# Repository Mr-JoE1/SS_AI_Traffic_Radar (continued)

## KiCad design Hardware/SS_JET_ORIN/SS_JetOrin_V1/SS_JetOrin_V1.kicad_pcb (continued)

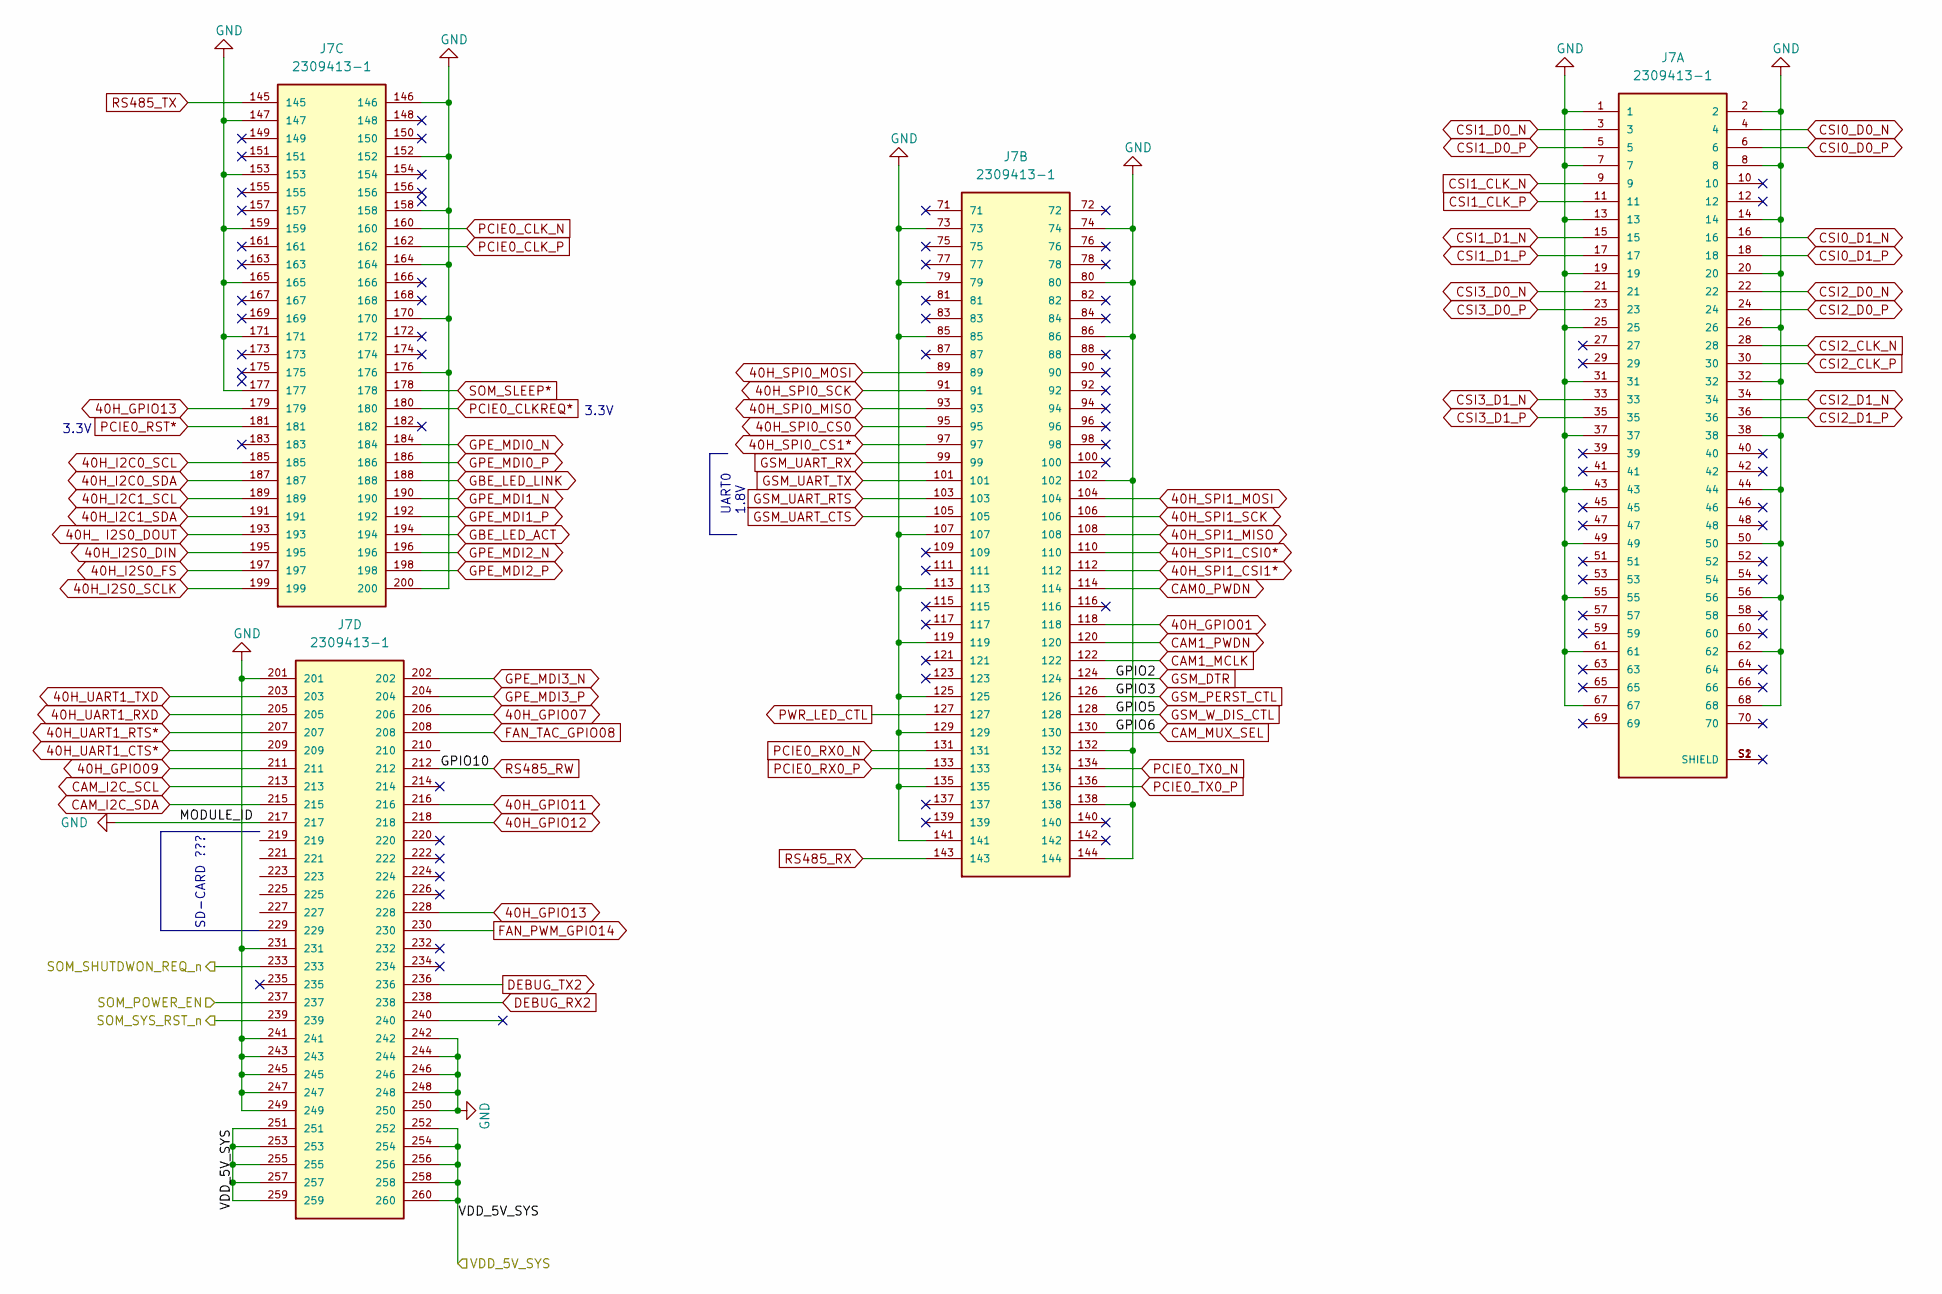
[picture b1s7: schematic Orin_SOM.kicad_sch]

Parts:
J7: 2309413-1; TE_2309413-1

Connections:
40H_ I2S0_DOUT: J7.193; also elsewhere on the board
40H_GPIO01: J7.118; also elsewhere on the board
40H_GPIO07: J7.206; also elsewhere on the board
40H_GPIO09: J7.211; also elsewhere on the board
40H_GPIO11: J7.216; also elsewhere on the board
40H_GPIO12: J7.218; also elsewhere on the board
40H_GPIO13: J7.179, J7.228; also elsewhere on the board
40H_I2C0_SCL: J7.185
40H_I2C0_SDA: J7.187
40H_I2C1_SCL: J7.189
40H_I2C1_SDA: J7.191
40H_I2S0_DIN: J7.195; also elsewhere on the board
40H_I2S0_FS: J7.197; also elsewhere on the board
40H_I2S0_SCLK: J7.199; also elsewhere on the board
40H_SPI0_CS0: J7.95; also elsewhere on the board
40H_SPI0_CS1*: J7.97; also elsewhere on the board
40H_SPI0_MISO: J7.93; also elsewhere on the board
40H_SPI0_MOSI: J7.89; also elsewhere on the board
40H_SPI0_SCK: J7.91; also elsewhere on the board
40H_SPI1_CSI0*: J7.110; also elsewhere on the board
40H_SPI1_CSI1*: J7.112; also elsewhere on the board
40H_SPI1_MISO: J7.108; also elsewhere on the board
40H_SPI1_MOSI: J7.104; also elsewhere on the board
40H_SPI1_SCK: J7.106; also elsewhere on the board
40H_UART1_CTS*: J7.209; also elsewhere on the board
40H_UART1_RTS*: J7.207; also elsewhere on the board
40H_UART1_RXD: J7.205; also elsewhere on the board
40H_UART1_TXD: J7.203; also elsewhere on the board
/Orin_SOM/SOM_POWER_EN: J7.237; also elsewhere on the board
/PSUs/P_Seq_M/SHUT_REQ: J7.233; also elsewhere on the board
/PSUs/P_Seq_M/SYS_RST: J7.239; also elsewhere on the board
/VDD_5V_SYS: J7.251, J7.252, J7.253, J7.254, J7.255, J7.256, J7.257, J7.258, J7.259, J7.260; also elsewhere on the board
CAM0_PWDN: J7.114; also elsewhere on the board
CAM1_MCLK: J7.122; also elsewhere on the board
CAM1_PWDN: J7.120; also elsewhere on the board
CAM_I2C_SCL: J7.213; also elsewhere on the board
CAM_I2C_SDA: J7.215; also elsewhere on the board
CAM_MUX_SEL: J7.130; also elsewhere on the board
CSI0_D0_N: J7.4; also elsewhere on the board
CSI0_D0_P: J7.6; also elsewhere on the board
CSI0_D1_N: J7.16; also elsewhere on the board
CSI0_D1_P: J7.18; also elsewhere on the board
CSI1_CLK_N: J7.9; also elsewhere on the board
CSI1_CLK_P: J7.11; also elsewhere on the board
CSI1_D0_N: J7.3; also elsewhere on the board
CSI1_D0_P: J7.5; also elsewhere on the board
CSI1_D1_N: J7.15; also elsewhere on the board
CSI1_D1_P: J7.17; also elsewhere on the board
CSI2_CLK_N: J7.28; also elsewhere on the board
CSI2_CLK_P: J7.30; also elsewhere on the board
CSI2_D0_N: J7.22; also elsewhere on the board
CSI2_D0_P: J7.24; also elsewhere on the board
CSI2_D1_N: J7.34; also elsewhere on the board
CSI2_D1_P: J7.36; also elsewhere on the board
CSI3_D0_N: J7.21; also elsewhere on the board
CSI3_D0_P: J7.23; also elsewhere on the board
CSI3_D1_N: J7.33; also elsewhere on the board
CSI3_D1_P: J7.35; also elsewhere on the board
DEBUG_RX2: J7.238; also elsewhere on the board
DEBUG_TX2: J7.236; also elsewhere on the board
FAN_PWM_GPIO14: J7.230; also elsewhere on the board
FAN_TAC_GPIO08: J7.208; also elsewhere on the board
GBE_LED_ACT: J7.194; also elsewhere on the board
GBE_LED_LINK: J7.188; also elsewhere on the board
GND: J7.1, J7.2, J7.7, J7.8, J7.13, J7.14, J7.19, J7.20, J7.25, J7.26, J7.31, J7.32, J7.37, J7.38, J7.43, J7.44, J7.49, J7.50, J7.55, J7.56, J7.61, J7.62, J7.67, J7.68, J7.73, J7.74, J7.79, J7.80, J7.85, J7.86, J7.102, J7.107, J7.113, J7.119, J7.125, J7.129, J7.132, J7.135, J7.138, J7.141, J7.144, J7.146, J7.147, J7.152, J7.153, J7.158, J7.159, J7.164, J7.165, J7.170, J7.171, J7.176, J7.177, J7.200, J7.201, J7.217, J7.231, J7.241, J7.242, J7.243, J7.244, J7.245, J7.246, J7.247, J7.248, J7.249, J7.250; also elsewhere on the board
GPE_MDI0_N: J7.184; also elsewhere on the board
GPE_MDI0_P: J7.186; also elsewhere on the board
GPE_MDI1_N: J7.190; also elsewhere on the board
GPE_MDI1_P: J7.192; also elsewhere on the board
GPE_MDI2_N: J7.196; also elsewhere on the board
GPE_MDI2_P: J7.198; also elsewhere on the board
GPE_MDI3_N: J7.202; also elsewhere on the board
GPE_MDI3_P: J7.204; also elsewhere on the board
GSM_DTR: J7.124; also elsewhere on the board
GSM_PERST_CTL: J7.126; also elsewhere on the board
GSM_UART_CTS: J7.105; also elsewhere on the board
GSM_UART_RTS: J7.103; also elsewhere on the board
GSM_UART_RX: J7.99; also elsewhere on the board
GSM_UART_TX: J7.101; also elsewhere on the board
GSM_W_DIS_CTL: J7.128; also elsewhere on the board
PCIE0_CLKREQ*: J7.180; also elsewhere on the board
PCIE0_CLK_N: J7.160; also elsewhere on the board
PCIE0_CLK_P: J7.162; also elsewhere on the board
PCIE0_RST*: J7.181; also elsewhere on the board
PCIE0_RX0_N: J7.131; also elsewhere on the board
PCIE0_RX0_P: J7.133; also elsewhere on the board
PCIE0_TX0_N: J7.134; also elsewhere on the board
PCIE0_TX0_P: J7.136; also elsewhere on the board
PWR_LED_CTL: J7.127; also elsewhere on the board
RS485_RW: J7.212; also elsewhere on the board
RS485_RX: J7.143; also elsewhere on the board
RS485_TX: J7.145; also elsewhere on the board
SOM_SLEEP*: J7.178; also elsewhere on the board

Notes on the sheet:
3.3V
SD-CARD ???
UART0 1.8V

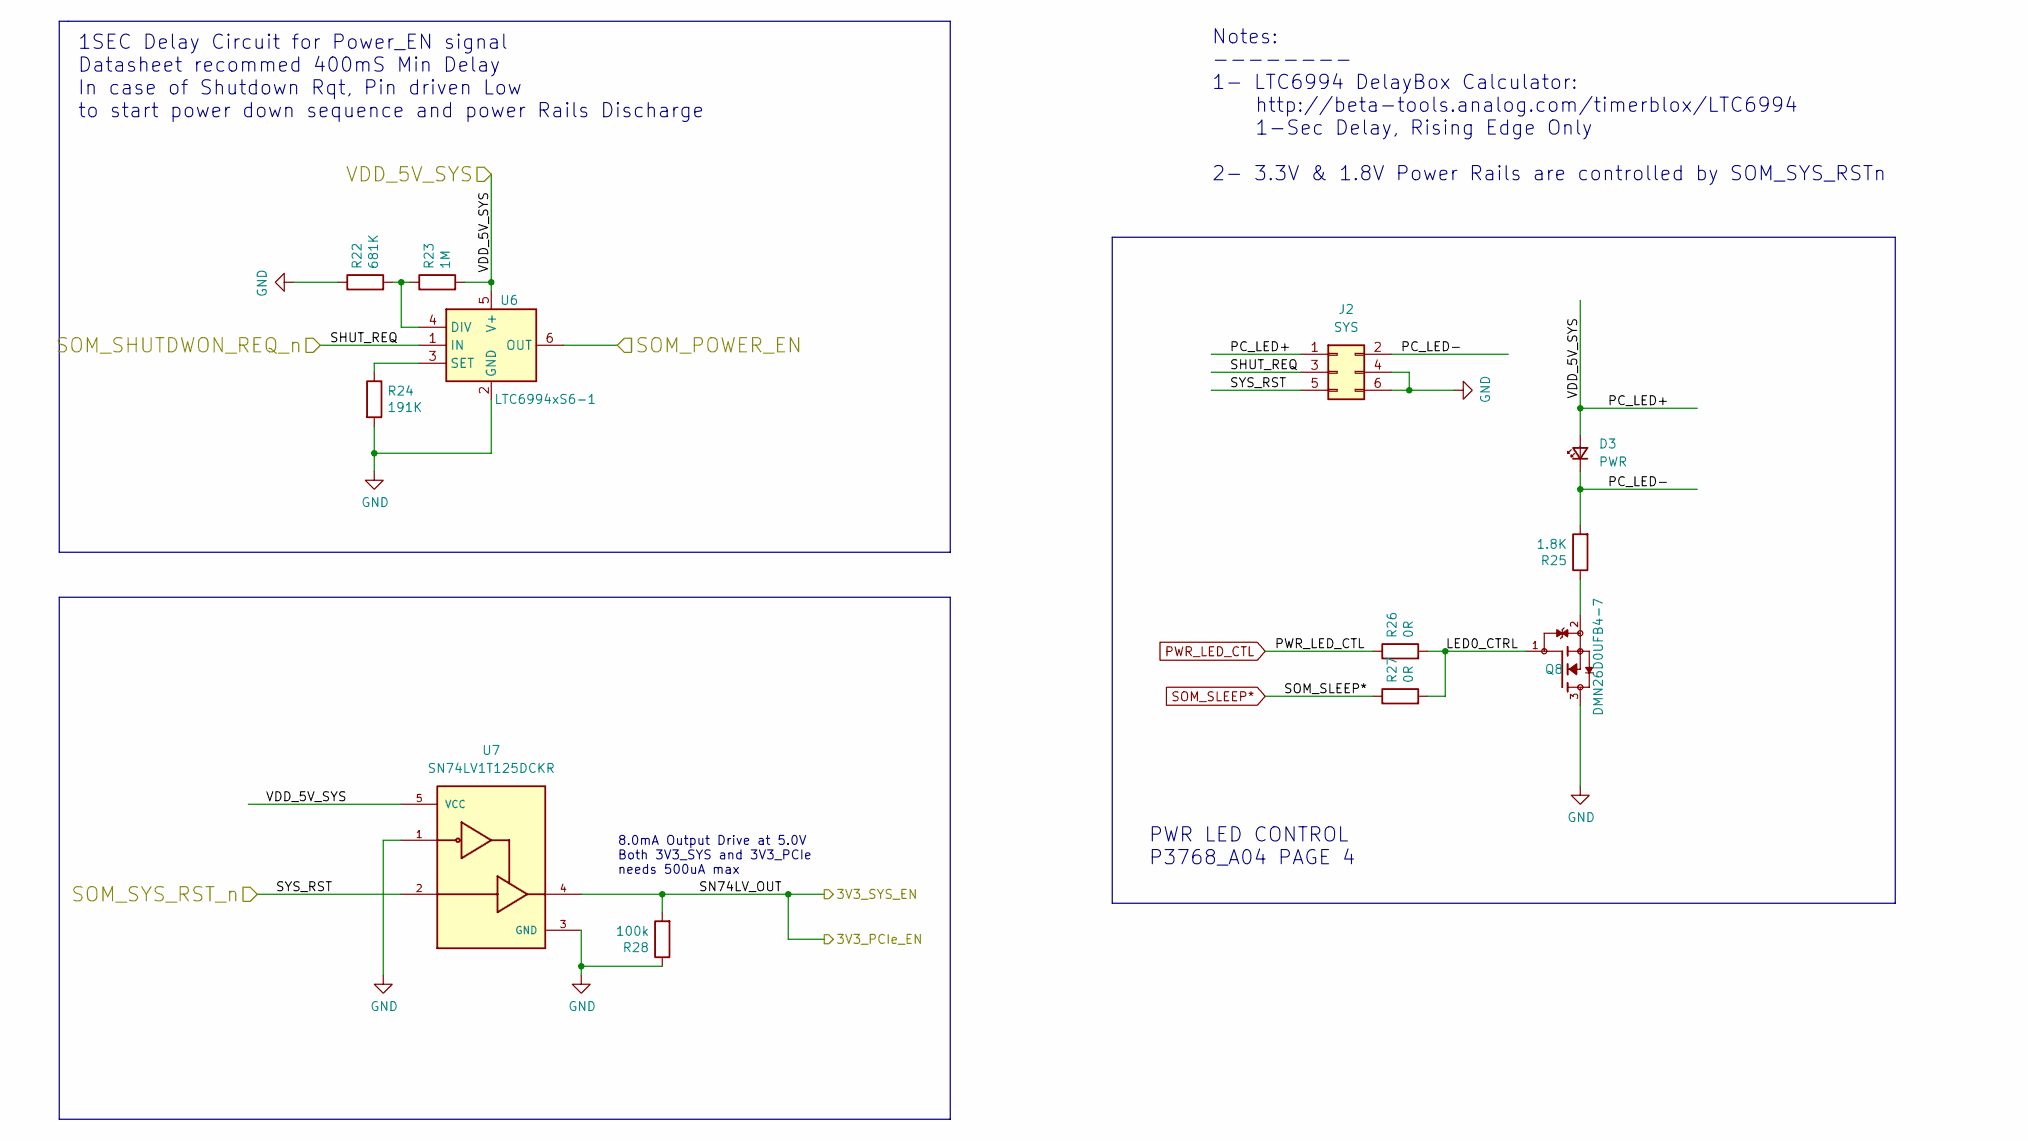
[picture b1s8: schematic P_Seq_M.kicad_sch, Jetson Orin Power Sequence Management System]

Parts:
D3: PWR; LED_0402_1005Metric; LCSC C130719
J2: SYS; PinHeader_2x03_P2.54mm_Vertical
Q8: DMN26D0UFB4-7; TRXDFN100X60X40-3N; PARTREV 12-2; LCSC C260867
R22: 681K; R_0201_0603Metric; Part Description Resistor 12K M1005 1% 63mW; LCSC C423447
R23: 1M; R_0201_0603Metric; Part Description Resistor 12K M1005 1% 63mW; LCSC C2105628
R24: 191K; R_0201_0603Metric; Part Description Resistor 12K M1005 1% 63mW; LCSC C778415
R25: 1.8K; R_0201_0603Metric; Part Description Resistor 12K M1005 1% 63mW; LCSC C171943
R26, R27: 0R; R_0201_0603Metric; Part Description Resistor 12K M1005 1% 63mW; LCSC C106228
R28: 100k; R_0201_0603Metric; Part Description Resistor 12K M1005 1% 63mW; LCSC C106224
U6: LTC6994xS6-1; TSOT-23-6; LCSC OUT_OS
U7: SN74LV1T125DCKR; SOT65P210X110-5N; PARTREV A; LCSC C75925

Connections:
/Orin_SOM/SOM_POWER_EN: U6.6 (OUT); also elsewhere on the board
/PSUs/3V3_PCIe_EN: R28.2, U7.4; also elsewhere on the board
/PSUs/P_Seq_M/LED0_CTRL: Q8.1, R26.2, R27.2
/PSUs/P_Seq_M/PC_LED-: D3.1 (K), J2.2, R25.2
/PSUs/P_Seq_M/SHUT_REQ: J2.3, U6.1 (IN); also elsewhere on the board
/PSUs/P_Seq_M/SYS_RST: J2.5, U7.2; also elsewhere on the board
/VDD_5V_SYS: D3.2 (A), J2.1, R23.2, U6.5 (V+), U7.5 (VCC); also elsewhere on the board
GND: J2.4, J2.6, Q8.3, R22.1, R24.2, R28.1, U6.2 (GND), U7.1, U7.3 (GND); also elsewhere on the board
unnamed: Q8.2, R25.1
unnamed: R22.2, R23.1, U6.4 (DIV)
unnamed: R24.1, U6.3 (SET)
PWR_LED_CTL: R26.1; also elsewhere on the board
SOM_SLEEP*: R27.1; also elsewhere on the board

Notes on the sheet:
1SEC Delay Circuit for Power_EN signal Datasheet recommed 400mS Min Delay In case of Shutdown Rqt, Pin driven Low to start power down sequence and power Rails Discharge
PWR LED CONTROL P3768_A04 PAGE 4
8.0mA Output Drive at 5.0V Both 3V3_SYS and 3V3_PCIe needs 500uA max
Notes: -------- 1- LTC6994 DelayBox Calculator: http://beta-tools.analog.com/timerblox/LTC6994 1-Sec Delay, Rising Edge Only 2- 3.3V & 1.8V Power Rails are controlled by SOM_SYS_RSTn

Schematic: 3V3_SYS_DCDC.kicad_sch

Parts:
C15: 470uF; Kemet _3760_H; LCSC C600599
C16: 100n; C_0201_0603Metric; LCSC C307380
C17: 470uF; CP_EIA-7343-31_Kemet-D; LCSC C116576
C18: 100n; C_0201_0603Metric; Part Description 0.1uF 10% 100V Ceramic Capacitor X5R 04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; LCSC C307380
C19: 33p; C_0201_0603Metric; LCSC C277477
C20: 10p; C_0201_0603Metric; LCSC C272871
Q4: DMN26D0UFB4-7; TRXDFN100X60X40-3N; PARTREV 12-2; LCSC C260867
Q5: DMN61D9UW; SOT65P210X110-3N; LCSC C151592
R6: 82K 1%; R_0201_0603Metric; LCSC C384402
R7: 51K; R_0201_0603Metric; LCSC C171974
R8: 470R; R_0201_0603Metric; LCSC C304545
R9: 47K 1%; R_0201_0603Metric; LCSC C138139
R10: 100K; R_0201_0603Metric; Part Description Resistor 12K M1005 1% 63mW; LCSC C106224
R11: 1.27; R_0201_0603Metric; Part Description Resistor 12K M1005 1% 63mW; LCSC C158692
TP3: TestPoint; TestPoint_Pad_D1.0mm
U3: MIC29302WU; TO-263-5_TabPin3; LCSC C11149

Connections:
/3v3_SYS: C17.1, C18.1, C19.1, C20.1, R6.1, R8.1, R11.1, TP3.1, U3.4 (VOUT); also elsewhere on the board
/PSUs/3V3_PCIe_EN: Q4.1, R7.1; also elsewhere on the board
/PSUs/+12v: C15.1, C16.1, U3.2 (VIN); also elsewhere on the board
/VDD_5V_SYS: R10.1; also elsewhere on the board
GND: C15.2, C16.2, C17.2, C18.2, C19.2, C20.2, Q4.2, Q5.2 (S), R8.2, R9.2, U3.3 (GND); also elsewhere on the board
unnamed: Q4.3, Q5.1 (G), R10.2
unnamed: Q5.3 (D), R11.2
unnamed: R6.2, R9.1, U3.5 (ADJ)
unnamed: R7.2, U3.1 (EN)

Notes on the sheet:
3A/3.3V PSU for PCIe Module NB: PCIe x1 takes a maximum of +12v @0.6A or +3.3v@3A , 10Watts combined
3V3_SYS Discharge Circuit - P3768 PAGE 10
LOW ESR

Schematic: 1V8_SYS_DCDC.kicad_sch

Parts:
C1: 4.7u; C_0201_0603Metric; LCSC C335103
C2: nf; C_0201_0603Metric
C3, C4, C5: 1u; C_0201_0603Metric; LCSC C87143
Q1: DMN26D0UFB4-7; TRXDFN100X60X40-3N; PARTREV 12-2; LCSC C260867
Q2: DMN61D9UW; SOT65P210X110-3N; LCSC C151592
R1: 100K; R_0201_0603Metric; Part Description Resistor 12K M1005 1% 63mW; LCSC C106224
R2: 5.6R; R_0201_0603Metric; Part Description Resistor 12K M1005 1% 63mW; LCSC C367405
TP6: TestPoint; TestPoint_Pad_D1.0mm
U1: AP2127K-1.8; SOT-23-5; LCSC C151375

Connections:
/1V8_SYS: C1.1, C2.1, R2.1, TP6.1, U1.5 (VOUT); also elsewhere on the board
/3v3_SYS: C3.1, C4.1, C5.1, U1.1 (VIN); also elsewhere on the board
/PSUs/3V3_PCIe_EN: Q1.1, U1.3 (EN); also elsewhere on the board
/VDD_5V_SYS: R1.1; also elsewhere on the board
GND: C1.2, C2.2, C3.2, C4.2, C5.2, Q1.2, Q2.2 (S), U1.2 (GND); also elsewhere on the board
unnamed: Q1.3, Q2.1 (G), R1.2
unnamed: Q2.3 (D), R2.2

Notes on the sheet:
1V8 Discharge Circuit - P3768 PAGE 11

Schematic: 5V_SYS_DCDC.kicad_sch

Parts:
C9, C10: 4.7uF; C_0402_1005Metric; Part Description 10uF 10% or 20% 35V Ceramic Capacitor X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; LCSC C2858031
C11, C14: 0.01uF; C_0201_0603Metric; LCSC C285010
C12: 330uF; CP_EIA-7343-31_Kemet-D; LCSC C105408
C13: 0.01uF; C_0201_0603Metric; Part Description 10uF 10% or 20% 35V Ceramic Capacitor X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; LCSC C285010
D2: SS54; D_SMA; LCSC C908681
L1: CDRH127/LDNP-150MC; L_12x12mm_H8mm; LCSC C879410
R4: 10K; R_0201_0603Metric; LCSC C106225
R5: 3.16K; R_0201_0603Metric; LCSC C367583
TP2: TestPoint; TestPoint_Pad_D1.0mm
U2: TPS5450DDAR; CONV_TPS5450DDAR; PARTREV D; LCSC C114425

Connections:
/PSUs/5V_SYS_DCDC/VSNS1: R4.2, R5.1, U2.4 (VSENSE)
/PSUs/+12v: C9.1, C10.1, C11.1, U2.7 (VIN); also elsewhere on the board
/VDD_5V_SYS: C12.1, C13.1, L1.2, R4.1, TP2.1; also elsewhere on the board
GND: C9.2, C10.2, C11.2, C12.2, C13.2, D2.1 (A), R5.2, U2.6 (GND), U2.9 (POWERPAD); also elsewhere on the board
unnamed: C14.1, U2.1 (BOOT)
unnamed: C14.2, D2.2 (K), L1.1, U2.8 (PH)

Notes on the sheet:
12V to 5V step down CONV 3A Normal Load 5A@MAX
-(P3768_PAGE 9) *They use 10A chip ! due to data sheet Orin SOM LOAD 5A MAX

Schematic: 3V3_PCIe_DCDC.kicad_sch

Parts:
C21, C27: 470uF; Kemet _3760_H; LCSC C600599
C22, C28: 100n; C_0201_0603Metric; LCSC C307380
C23, C29: 470uF; CP_EIA-7343-31_Kemet-D; LCSC C116576
C24, C30: 100n; C_0201_0603Metric; Part Description 0.1uF 10% 100V Ceramic Capacitor X5R 04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; LCSC C307380
C25, C31: 33p; C_0201_0603Metric; LCSC C277477
C26, C32: 10p; C_0201_0603Metric; LCSC C272871
Q6: DMN26D0UFB4-7; TRXDFN100X60X40-3N; PARTREV 12-2; LCSC C260867
Q7: DMN61D9UW; SOT65P210X110-3N; LCSC C151592
R12, R18: 82K 1%; R_0201_0603Metric; LCSC C384402
R13: 100K; R_0201_0603Metric; Part Description Resistor 12K M1005 1% 63mW; LCSC C106224
R14: 1.27; R_0201_0603Metric; Part Description Resistor 12K M1005 1% 63mW; LCSC C2691510
R15, R19: 51K; R_0201_0603Metric; LCSC C171974
R16, R20: 470R; R_0201_0603Metric; LCSC C304545
R17, R21: 47K 1%; R_0201_0603Metric; LCSC C138139
TP4, TP5: TestPoint; TestPoint_Pad_D1.0mm
U4, U5: MIC29302WU; TO-263-5_TabPin3; LCSC C11149

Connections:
/3v3_PCIe: C23.1, C24.1, C25.1, C26.1, C29.1, C30.1, C31.1, C32.1, R12.1, R14.1, R16.1, R18.1, R20.1, TP4.1, TP5.1, U4.4 (VOUT), U5.4 (VOUT); also elsewhere on the board
/PSUs/3V3_PCIe_DCDC/3V3_SYS_EN: Q6.1, R15.1, R19.1
/PSUs/+12v: C21.1, C22.1, C27.1, C28.1, U4.2 (VIN), U5.2 (VIN); also elsewhere on the board
/VDD_5V_SYS: R13.1; also elsewhere on the board
GND: C21.2, C22.2, C23.2, C24.2, C25.2, C26.2, C27.2, C28.2, C29.2, C30.2, C31.2, C32.2, Q6.2, Q7.2 (S), R16.2, R17.2, R20.2, R21.2, U4.3 (GND), U5.3 (GND); also elsewhere on the board
unnamed: Q6.3, Q7.1 (G), R13.2
unnamed: Q7.3 (D), R14.2
unnamed: R12.2, R17.1, U4.5 (ADJ)
unnamed: R15.2, U4.1 (EN)
unnamed: R18.2, R21.1, U5.5 (ADJ)
unnamed: R19.2, U5.1 (EN)

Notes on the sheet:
3V3_SYS Discharge Circuit - P3768 PAGE 10
3A/3.3V PSU for PCIe Module NB: PCIe x1 takes a maximum of +12v @0.6A or +3.3v@3A , 10Watts combined
LOW ESR

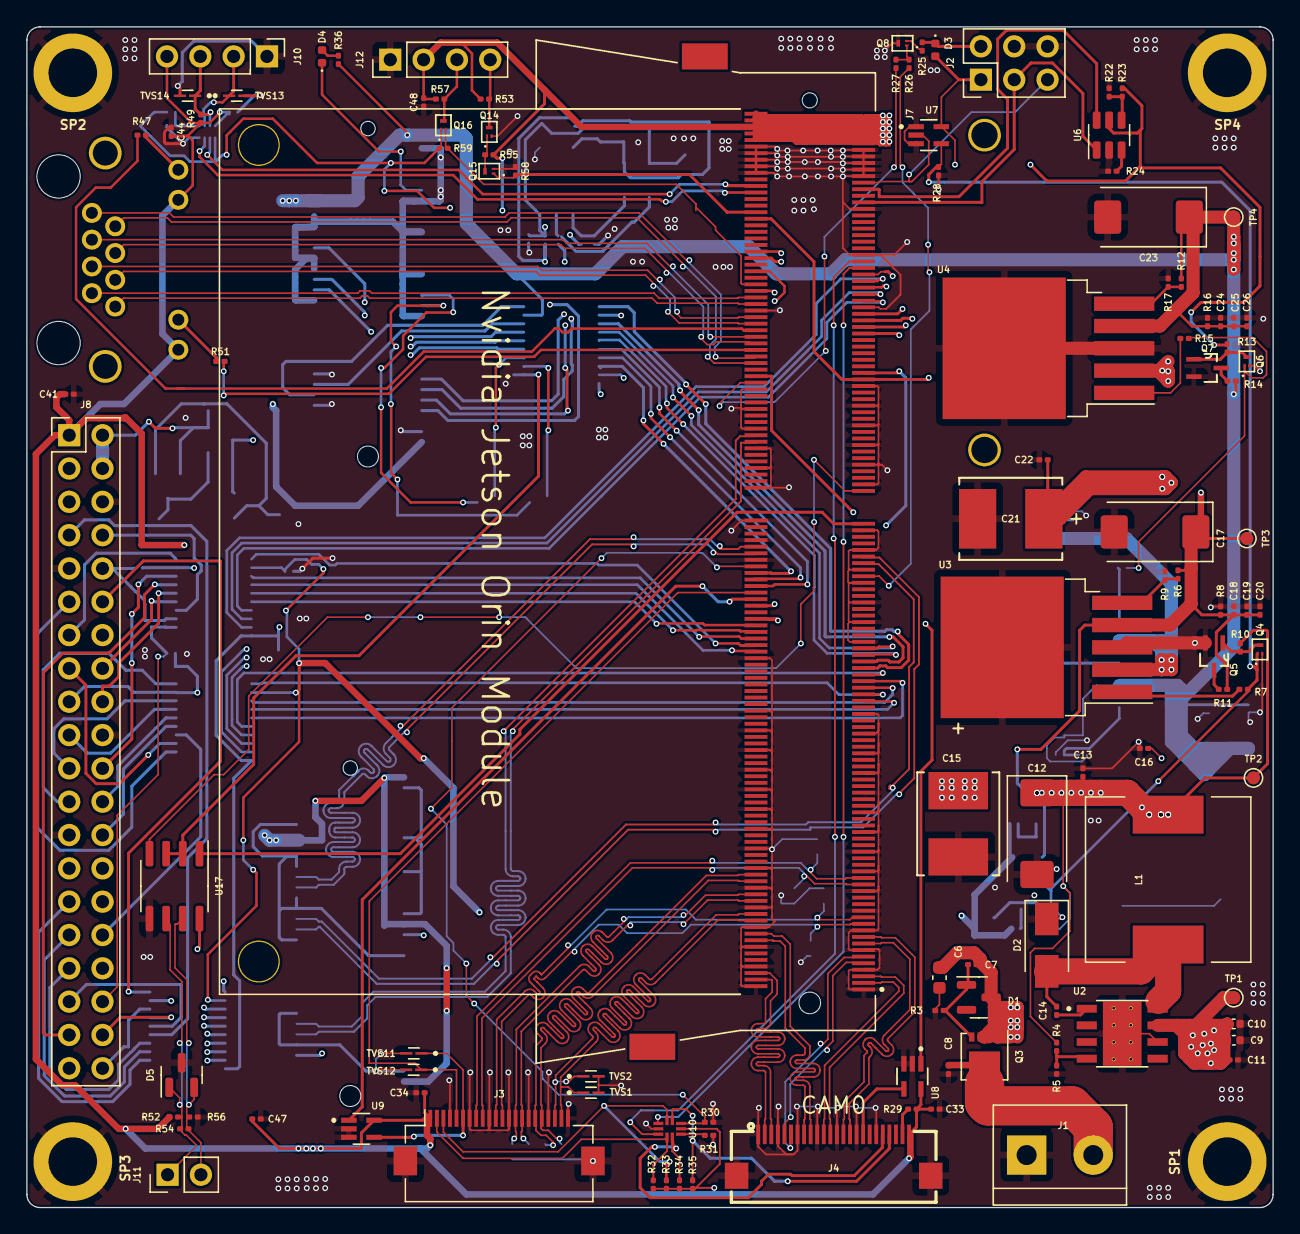
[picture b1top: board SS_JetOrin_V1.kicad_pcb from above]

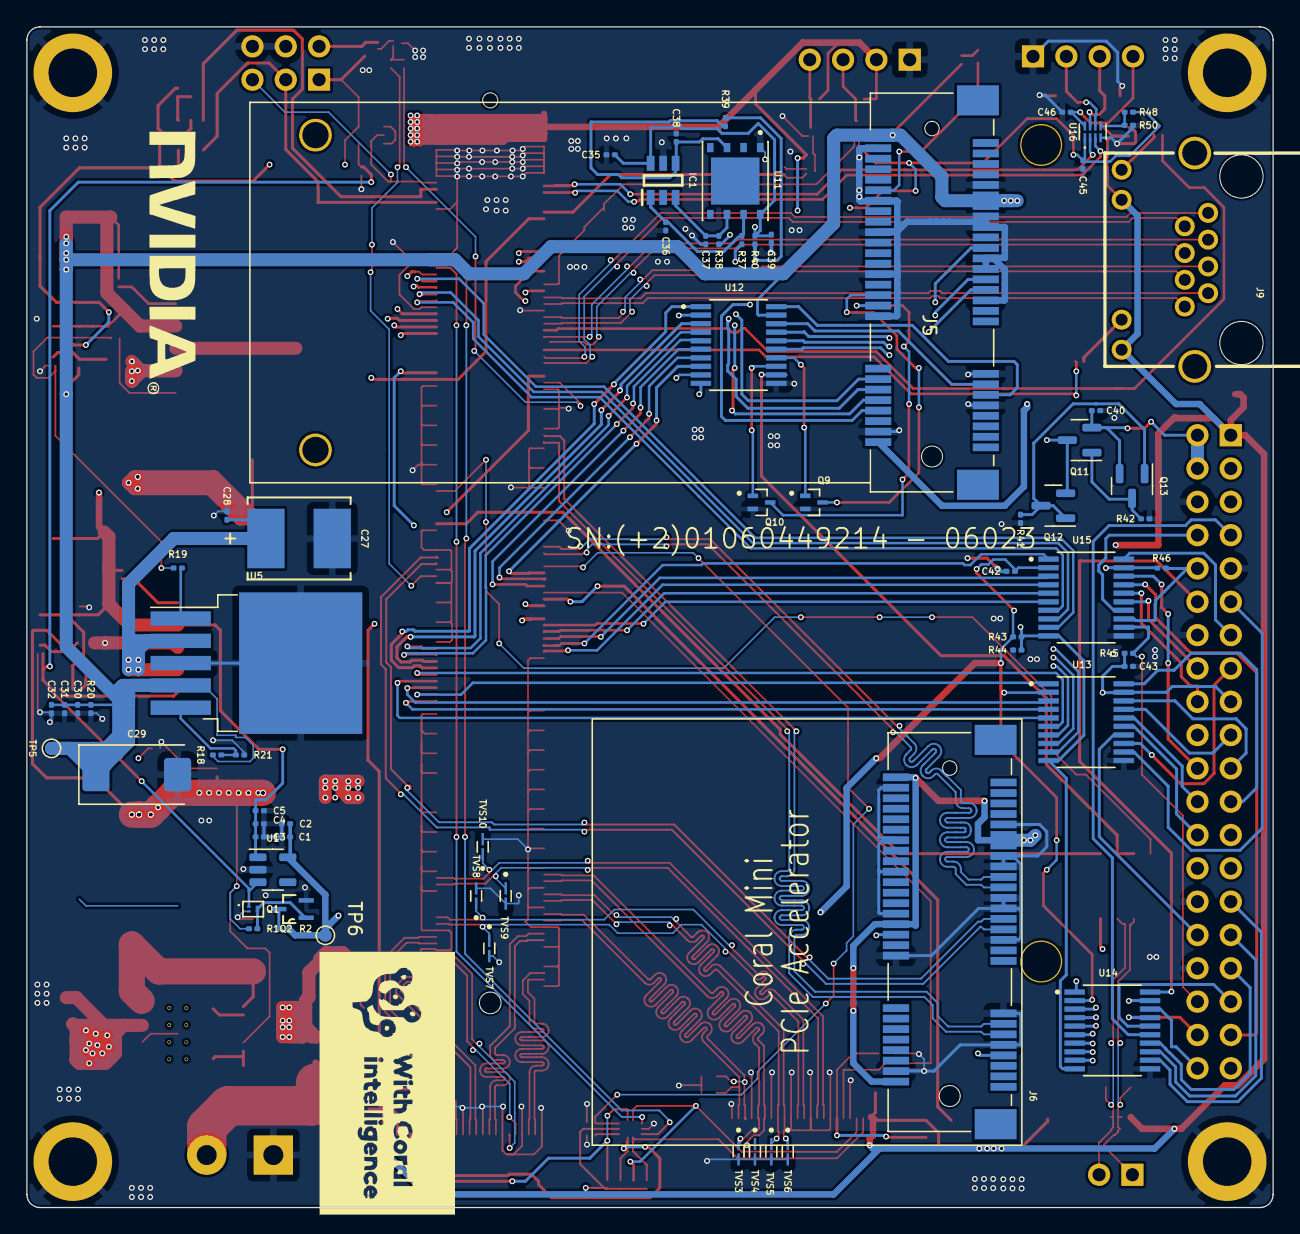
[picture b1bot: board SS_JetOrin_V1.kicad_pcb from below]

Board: 4 copper layers, 95.0 x 90.0 mm, 183 parts (68 on the bottom side), 182 nets.

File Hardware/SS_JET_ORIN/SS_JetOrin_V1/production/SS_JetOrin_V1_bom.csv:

Designator,Footprint,Quantity,Value,LCSC Part #
C1,0201,1,4.7u,C335103
"C10, C9",0402,2,4.7uF,C2858031
"C11, C13, C14",0201,3,0.01uF,C285010
C12,CP_EIA-7343-31_Kemet-D,1,330uF,C105408
"C15, C21, C27",Kemet _3760_H,3,470uF,C600599
"C16, C18, C22, C24, C28, C30, C34, C39, C40, C41, C42, C43, C44, C45, C46, C48, C7, C8",0201,18,100n,C307380
"C17, C23, C29",CP_EIA-7343-31_Kemet-D,3,470uF,C116576
"C19, C25, C31, C35, C36, C37, C38",0201,7,33p,C277477
C2,0201,1,nf,
"C20, C26, C32",0201,3,10p,C272871
"C3, C33, C4, C5",0201,4,1u,C87143
C47,0201,1,104,C307380
C6,0603,1,10u 35v,C194427
D1,SOT-23,1,MMBZ5242BLT1G,C236184
D2,D_SMA,1,SS54,C908681
D3,0402,1,PWR,C130719
D4,0402,1,W,C130724
D5,SOT-23,1,PSM712-LF-T7,C32677
IC1,SOT95P280X145-6N,1,DALC208SC6,C5123934
J1,TerminalBlock_bornier-2_P5.08mm,1,pwr,C3018698
J10,PinHeader_1x04_P2.54mm_Vertical,1,DEBUG,
J11,PinHeader_1x02_P2.54mm_Vertical,1,Conn_01x02_Male,
J12,PinHeader_1x04_P2.54mm_Vertical,1,FAN,C5116483
J2,PinHeader_2x03_P2.54mm_Vertical,1,SYS,
J3,Hirose_FH12-22S-0.5SH_1x22-1MP_P0.50mm_Horizontal,1,CAM1,C262668
J4,FPC-SMD_P0.50-24P_QCHF-SM-H2.0,1,CAM0,C262683
J5,Quectel_EG25-G_Mini_PCIe,1,Bus_PCI_Express_Mini,C266899
J6,BUS_PCI_Express_Mini_Half,1,Bus_PCI_Express_Mini,C266899
J7,TE_2309413-1,1,2309413-1,
J8,PinHeader_2x20_P2.54mm_Vertical,1,Conn_02x20_Odd_Even,
J9,RJ45-TH_R-RJ45R08P-C000,1,RJ45_LED_Shielded,C386757
L1,L_12x12mm_H8mm,1,CDRH127/LDNP-150MC,C879410
"Q1, Q14, Q15, Q16, Q4, Q6, Q8",TRXDFN100X60X40-3N,7,DMN26D0UFB4-7,C260867
"Q10, Q9",SOTFL50P160X85-3N,2,DTC143ZEBTL,C308696
Q11,SOT-23,1,NX2301P,C191273
"Q12, Q13",SOT-23,2,BC857B,C556165
"Q2, Q5, Q7",SOT65P210X110-3N,3,DMN61D9UW,C151592
Q3,Diodes_PowerDI3333-8,1,DMP3013SFV-7,C264098
"R1, R10, R13, R28, R41, R45, R46, R49, R50",0201,9,100K,C106224
"R11, R14",0201,2,1.27,C2691510
"R12, R18, R6",0201,3,82K 1%,C384402
"R15, R19, R7",0201,3,51K,C171974
"R16, R20, R8",0201,3,470R,C304545
"R17, R21, R9",0201,3,47K 1%,C138139
R2,0201,1,5.6R,C367405
R22,0201,1,681K,C423447
R23,0201,1,1M,C2105628
R24,0201,1,191K,C778415
R25,0201,1,1.8K,C171943
"R26, R27, R31, R48",0201,4,0R,C106228
"R29, R32, R33, R34, R35, R36, R55",0201,7,1K,C131396
R3,0201,1,12K 1%,C226413
"R30, R4, R53, R57, R58, R59",0201,6,10K,C106225
"R37, R38, R39",0201,3,22R,C155743
R40,0201,1,15K,C965337
R42,0201,1,47K,C138139
R43,0201,1,20K,C295787
R44,0201,1,2M,C106228
"R47, R51, R54",0201,3,120R,C295718
R5,0201,1,3.16K,C367583
R52,0201,1,360R ,C2930003
R56,0201,1,360R,C2930003
"SP1, SP2, SP3, SP4",9774060151,4,9774060151,9774060151
TP1,TestPoint_Pad_D1.0mm,1,12V,
"TP2, TP3, TP4, TP5, TP6",TestPoint_Pad_D1.0mm,5,TestPoint,
"TVS1, TVS10, TVS11, TVS12, TVS13, TVS14, TVS2, TVS3, TVS4, TVS5, TVS6, TVS7, TVS8, TVS9",DIOM1006X40N,14,ESD9L5.0ST5G,C2682269
U1,SOT-23-5,1,AP2127K-1.8,C151375
U10,QFN40P140X180X55-10N,1,TS3USB30ERSWR,TS3USB30ERSWR
U11,PSON127P500X600X82-9N,1,SIM-E-MFF2-GL-250,
"U12, U13, U14, U15",SOP65P640X120-20N,4,TXB0108PWR,C53406
U16,IC_TXB0302DQMR,1,TXB0302DQMR,C2652938
U17,SOIC-8_3.9x4.9mm_P1.27mm,1,MAX3485,C9943
U2,CONV_TPS5450DDAR,1,TPS5450DDAR,C114425 
"U3, U4, U5",TO-263-5_TabPin3,3,MIC29302WU,C11149
U6,TSOT-23-6,1,LTC6994xS6-1,OUT_OS
"U7, U8, U9",SOT65P210X110-5N,3,SN74LV1T125DCKR,C75925
